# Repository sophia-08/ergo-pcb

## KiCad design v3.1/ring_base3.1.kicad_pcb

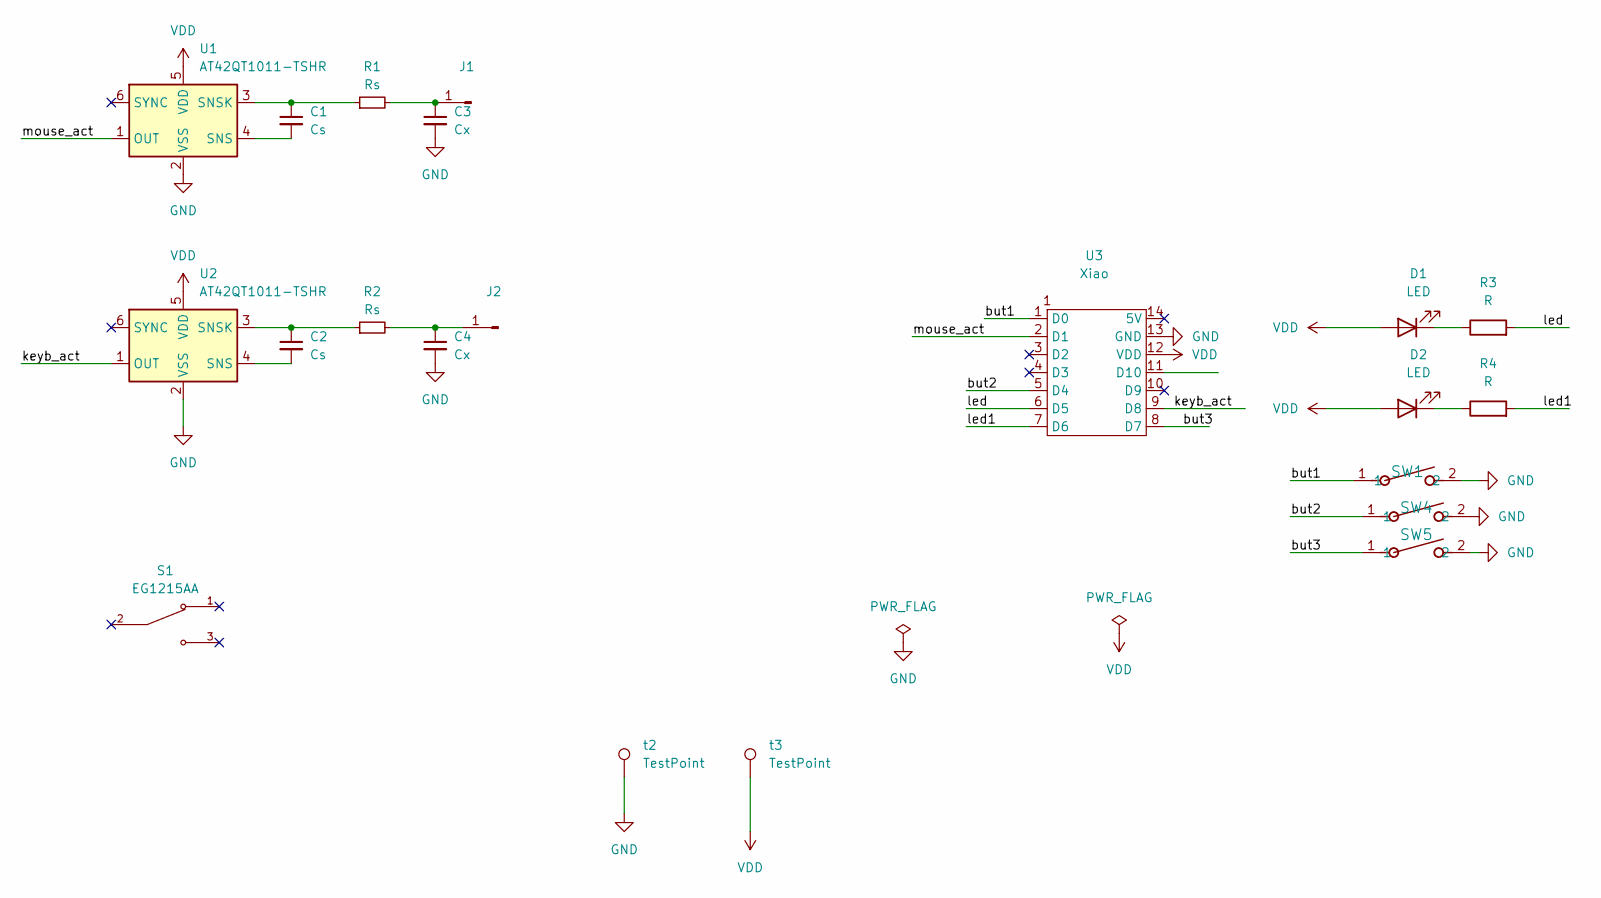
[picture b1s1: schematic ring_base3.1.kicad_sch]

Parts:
C1, C2: Cs; C_0402_1005Metric_Pad0.74x0.62mm_HandSolder
C3, C4: Cx; C_0402_1005Metric_Pad0.74x0.62mm_HandSolder
D1, D2: LED; LED_0603_1608Metric_Pad1.05x0.95mm_HandSolder
J1, J2: Conn_01x01_Pin; TestPoint_Pad_D1.0mm
R1, R2: Rs; R_0402_1005Metric_Pad0.72x0.64mm_HandSolder
R3, R4: R; R_0402_1005Metric_Pad0.72x0.64mm_HandSolder
S1: EG1215AA; SW_EG1215AA_no_hold; PARTREV A
SW1, SW4, SW5: TL1015AF160QG; SW_F160QG_EWI
U1, U2: AT42QT1011-TSHR; SOT-23-6
U3: Xiao; Seeed Xiao_actual_size_hold
t2, t3: TestPoint; TestPoint_Pad_D1.0mm

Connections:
/but1: SW1.1, U3.1 (D0)
/but2: SW4.1, U3.5 (D4)
/but3: SW5.1, U3.8 (D7)
/keyb_act: U2.1 (OUT), U3.9 (D8)
/led: R3.2, U3.6 (D5)
/led1: R4.2, U3.7 (D6)
/mouse_act: U1.1 (OUT), U3.2 (D1)
GND: C3.2, C4.2, SW1.2, SW4.2, SW5.2, U1.2 (VSS), U2.2 (VSS), U3.13 (GND), t2.1
unnamed: D1.1 (K), R3.1
unnamed: D2.1 (K), R4.1
unnamed: C3.1, J1.1, R1.2
unnamed: C4.1, J2.1, R2.2
unnamed: C1.2, U1.4 (SNS)
unnamed: C1.1, R1.1, U1.3 (SNSK)
unnamed: C2.2, U2.4 (SNS)
unnamed: C2.1, R2.1, U2.3 (SNSK)
VDD: D1.2 (A), D2.2 (A), U1.5 (VDD), U2.5 (VDD), U3.12 (VDD), t3.1

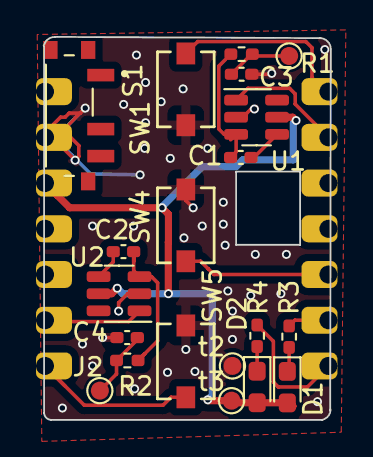
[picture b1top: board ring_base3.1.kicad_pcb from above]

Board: 2 copper layers, 16.0 x 21.3 mm, 21 parts (1 on the bottom side), 17 nets.

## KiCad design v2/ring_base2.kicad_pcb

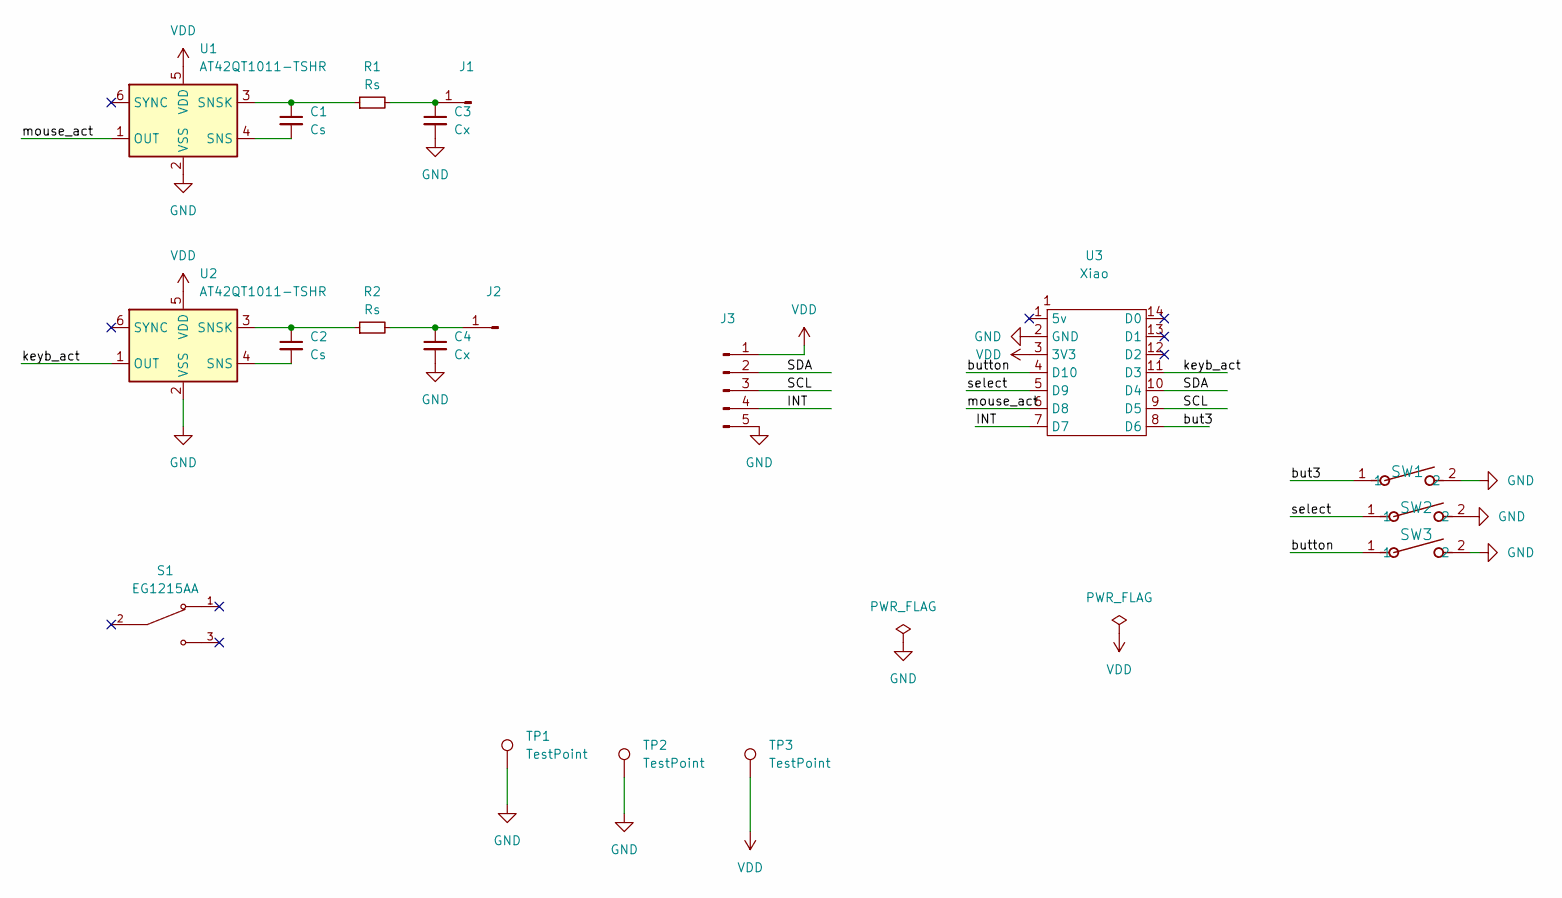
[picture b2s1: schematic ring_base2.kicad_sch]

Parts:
C1, C2: Cs; C_0402_1005Metric_Pad0.74x0.62mm_HandSolder
C3, C4: Cx; C_0402_1005Metric_Pad0.74x0.62mm_HandSolder
J1, J2: Conn_01x01_Pin; TestPoint_Pad_D1.5mm
J3: Conn_01x05_Pin; PinHeader_1x05_P2.54mm_Vertical
R1, R2: Rs; R_0402_1005Metric_Pad0.72x0.64mm_HandSolder
S1: EG1215AA; SW_EG1215AA; PARTREV A
SW1, SW2, SW3: TL1015AF160QG; SW_F160QG_EWI
TP1, TP2, TP3: TestPoint; TestPoint_Pad_D1.0mm
U1, U2: AT42QT1011-TSHR; SOT-23-6
U3: Xiao; Seeed Xiao

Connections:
/INT: J3.4, U3.7 (D7)
/SCL: J3.3, U3.9 (D5)
/SDA: J3.2, U3.10 (D4)
/but3: SW1.1, U3.8 (D6)
/button: SW3.1, U3.4 (D10)
/keyb_act: U2.1 (OUT), U3.11 (D3)
/mouse_act: U1.1 (OUT), U3.6 (D8)
/select: SW2.1, U3.5 (D9)
GND: C3.2, C4.2, J3.5, SW1.2, SW2.2, SW3.2, TP1.1, TP2.1, U1.2 (VSS), U2.2 (VSS), U3.2 (GND)
unnamed: C3.1, J1.1, R1.2
unnamed: C4.1, J2.1, R2.2
unnamed: C1.2, U1.4 (SNS)
unnamed: C1.1, R1.1, U1.3 (SNSK)
unnamed: C2.2, U2.4 (SNS)
unnamed: C2.1, R2.1, U2.3 (SNSK)
VDD: J3.1, TP3.1, U1.5 (VDD), U2.5 (VDD), U3.3 (3V3)

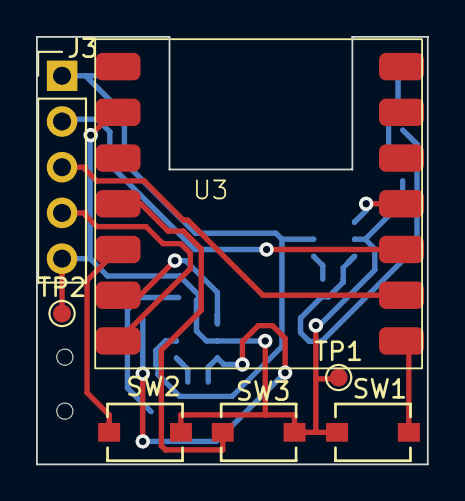
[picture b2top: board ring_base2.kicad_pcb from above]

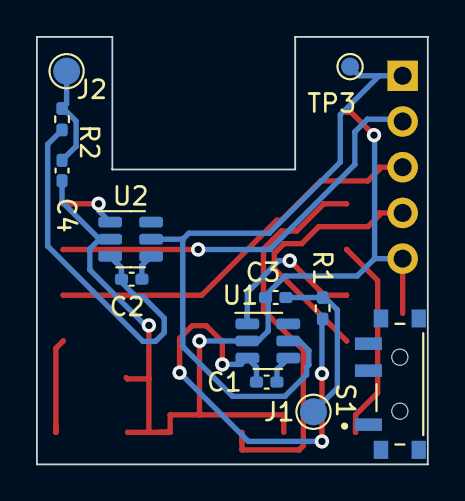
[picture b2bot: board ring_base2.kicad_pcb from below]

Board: 2 copper layers, 21.7 x 23.7 mm, 19 parts (12 on the bottom side), 16 nets.

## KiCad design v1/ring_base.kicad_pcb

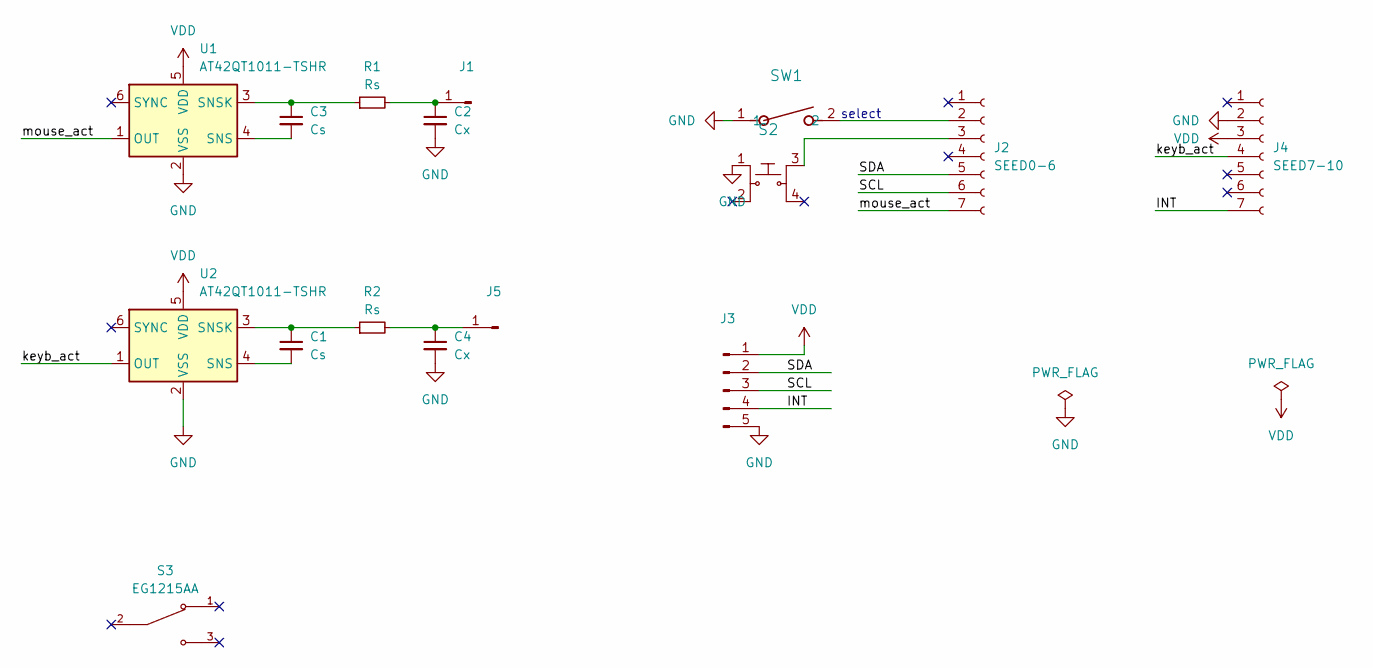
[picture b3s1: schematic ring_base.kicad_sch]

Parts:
C1, C3: Cs; C_0402_1005Metric_Pad0.74x0.62mm_HandSolder
C2, C4: Cx; C_0402_1005Metric_Pad0.74x0.62mm_HandSolder
J1, J5: Conn_01x01_Pin; TestPoint_Pad_D2.0mm
J2: SEED0-6; PinHeader_1x07_P2.54mm_Vertical
J3: Conn_01x05_Pin; PinHeader_1x05_P2.54mm_Vertical
J4: SEED7-10; PinHeader_1x07_P2.54mm_Vertical
R1, R2: Rs; R_0402_1005Metric_Pad0.72x0.64mm_HandSolder
S2: PTS645SM43SMTR92_LFS; Switch_Tactile_SMD_6x6mm_PTS645; MPN PTS645SM43SMTR92 LFS; Digi-Key_PN CKN9112CT-ND
S3: EG1215AA; SW_EG1215AA; PARTREV A
SW1: TL1015AF160QG; SW_F160QG_EWI
U1, U2: AT42QT1011-TSHR; SOT-23-6

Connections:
/INT: J3.4, J4.7
/SCL: J2.6, J3.3
/SDA: J2.5, J3.2
/keyb_act: J4.4, U2.1 (OUT)
/mouse_act: J2.7, U1.1 (OUT)
GND: C2.2, C4.2, J3.5, J4.2, S2.1, SW1.1, U1.2 (VSS), U2.2 (VSS)
unnamed: C2.1, J1.1, R1.2
unnamed: J2.2, SW1.2
unnamed: J2.3, S2.3
unnamed: C4.1, J5.1, R2.2
unnamed: C3.2, U1.4 (SNS)
unnamed: C3.1, R1.1, U1.3 (SNSK)
unnamed: C1.2, U2.4 (SNS)
unnamed: C1.1, R2.1, U2.3 (SNSK)
VDD: J3.1, J4.3, U1.5 (VDD), U2.5 (VDD)

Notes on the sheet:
select

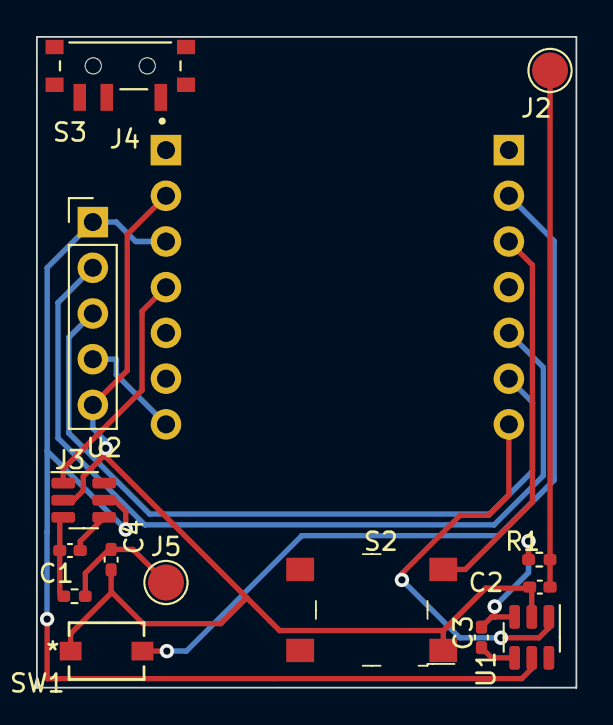
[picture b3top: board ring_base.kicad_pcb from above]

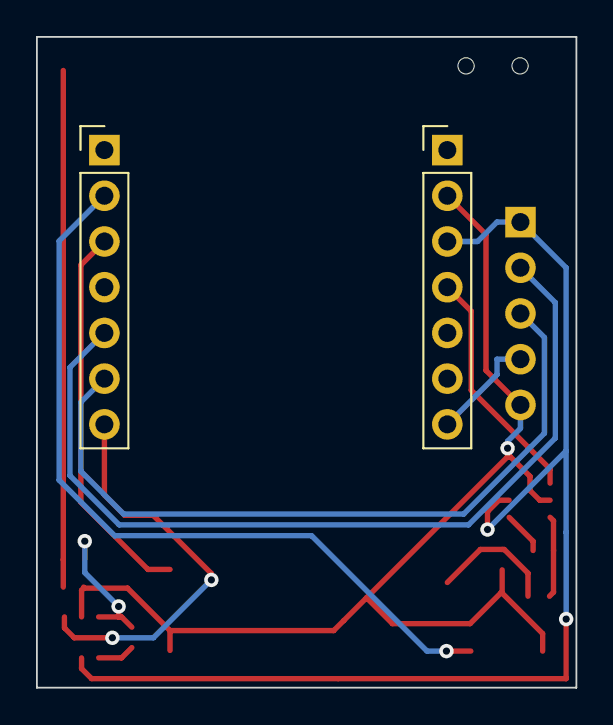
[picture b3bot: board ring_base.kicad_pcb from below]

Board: 2 copper layers, 30.0 x 36.2 mm, 16 parts (2 on the bottom side), 15 nets.

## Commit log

2024-08-08 pcb for Ergo ring
2024-08-15 Move to v1 folder
2024-09-11 Version 3
2024-09-14 v3.1
2025-01-21 a small fix
2025-01-24 Update pcb
